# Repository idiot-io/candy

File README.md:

more at [idiot.io](idiot.io)

# candy
Electrodible lolliPCBpops

34c3 [video](https://www.youtube.com/watch?v=yhNaNCrcmBk) cooking show and talk  

## tools
using [inkscape](https://inkscape.org) with [svg2shenzen](https://github.com/badgeek/svg2shenzhen) extension - a wrapper/fork to [Kicad's](https://kicad.github.io) own bitmap2component plugin.  
basicly - design a board in SVG vector format and export it as gerber files, ready for fabrication.  

included in the repo is a script to automate the gerber file generation.  
so after you run `extensins>svg2shenzhen>export`  
run  
```python2 ../kicad_gerber_gen.py IRiotCandy-svg2shnzn.kicad_pcb```

[gerbv](http://gerbv.geda-project.org) was then used to preview the gerber output and move the silkscreen to its right position. if you have it in your path, the previous python script should auto open the generate dgerber files fo you.

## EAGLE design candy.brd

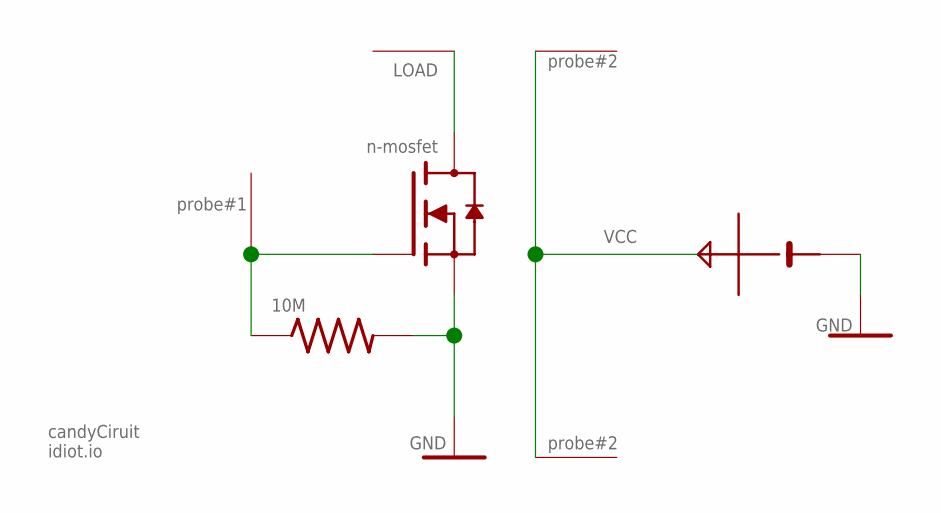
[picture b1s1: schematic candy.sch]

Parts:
10M: R-US_R1206; R1206
N-MOSFET: n-mosfet; SOT323
U$1, U$4, U$5: SMDPAD; PADSMD
U$7: CR2032LINX; CR2032-LINX
VCC: SMDPAD; PADSMD

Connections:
GND: 10M.2, N-MOSFET.2S (S), U$7.-
LOAD: N-MOSFET.3D (D), U$4.P$1
unnamed: 10M.1, N-MOSFET.1G (G), U$1.P$1
VCC: U$5.P$1, U$7.+, U$7.+2 (+), VCC.P$1

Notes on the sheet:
probe#1
probe#2
candyCiruit idiot.io

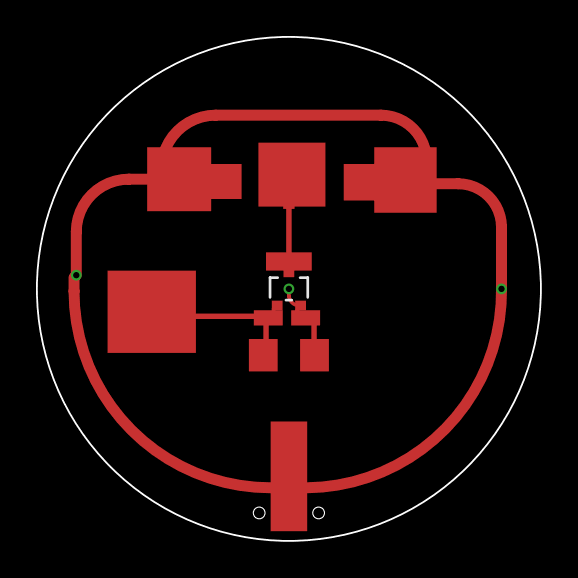
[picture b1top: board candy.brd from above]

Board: 2 copper layers, 28.0 x 28.0 mm, 7 parts (1 on the bottom side), 4 nets.

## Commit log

2018-03-08 inkscape svg
2018-03-08 layred for pdf2gerber
2018-03-08 eagle
2018-03-08 has candy, too big pads
2018-03-09 with ugly polygons on layout
2018-03-09 svg of eagle work
2018-03-09 added front
2018-03-10 BasicCandySilk update!
2018-03-10 BasicCandySilkScreenFinal
2018-03-10 BasicCandySilkFinal2
2018-03-10 FINALXXX
2018-03-12 fixed schema and added 2n222
2018-03-12 board ready for silk
2018-03-12 removed frame
2018-03-12 stright gerber
2018-03-12 folder
2018-03-13 shifted a bit
2018-03-15 CoinCellHolder
2018-03-15 coinCellDataSheet
2018-03-15 coinCell2models
2018-03-15 finall
2018-03-15 coinHolderPDF
2018-03-15 FINALLLL
2018-03-15 PDFFffffff
2018-05-16 no pours, smd and npn
2018-05-17 stick on front
2018-05-17 added svg, removed bmps
2018-05-17 gerber with svg2shanzen
2018-05-17 gerber ready
2018-05-18 3x3 and v1.0
2018-05-19 thermo cnady
2018-05-19 added mask
2018-05-19 bat back
2018-05-19 mask tweaks
2018-05-20 ModifiedSilkScreen
2018-05-20 updatedSilkSigns
2018-05-20 addedLM35Part
2018-05-21 resort
2018-05-21 removed dups
2018-05-22 IRiot candy
2018-05-22 reorder
2018-05-22 removed
2018-06-02 added Mosfet connections
2018-06-02 added v1.0 on back silk
2018-06-10 round vcc copper
2018-06-10 minor changs to iRiot board
2018-06-14 merged all files from IRiot repo
2018-06-15 shrink mask, and ass some silk guides
2018-06-15 silk/mask tweeks
2018-06-19 panelize in inkscape
2018-06-19 drills needs to be merged
2018-06-19 first gerber, need to remove copper aroudn drills
2018-06-19 some pics
2018-06-21 inkscape panel
2018-06-21 moved files
2018-06-22 panel 3mm border
2018-06-22 consolidated layers
2018-06-22 ready for multi panel
2018-06-22 3mm border gerbers
2018-06-23 new Graphics on krack
    added idiot.io logos on krakkk
2018-06-23 iirot esp8266 namechange
2018-06-23 added logos on Copper layer
    +changes
2018-06-23 final
2018-06-23 added IR&LED silk on IRiot
2018-06-23 added LM35
2018-06-23 added new GND GFX
    DONE!!!
2018-06-23 last!
2018-06-23 gitignore
2018-06-23 panel
2018-06-23 new panel
2018-06-24 wip mask
2018-06-25 draft panel, golden mask
2018-06-25 shrink edge top copper
2018-06-25 single
2018-06-26 upped the drill size to 0.4mm
2018-06-26 sent to fab
2018-06-27 thinner outlines, more back ground space
2018-07-03 nicer svg png
2018-07-05 restructure dirs
2018-07-09 add oled screen
2018-07-09 firemware comment
2018-07-10 post v1.1 changes #1
2018-07-10 added v1.2+
    all numbers are in seperate layer and
    also fixed logo silkscreen on both sides
2018-07-12 stick
2018-07-19 svg corrrections
2018-07-19 128x32 anel
2018-07-23 kicad idiot.io parts
2018-07-23 remove kicad lib to its own repo https://github.com/idiot-io/idiot-io-assets
2018-07-24 top breakouts
2018-07-25 bottom tab only
2018-07-26 bottom only tab
2018-08-01 flip led pin in iriot code, no random nec ir, svg bottom panel
2018-09-03 single basic
2018-12-23 G island
2018-12-23 v1.3
    fixed +3v and v1.3
2018-12-23 v1.3 throat
2018-12-24 releases folder
2018-12-24 release endyear
2019-01-30 added bitcraze svg2shnz
2019-01-30 renamed
2019-01-30 bitbadge svg2chnzn
2019-02-02 v1.0
2019-02-02 centered
2019-02-02 added name to b.silk
2019-02-02 Gpad fixed
2019-02-02 GpadMask fixed
2019-02-02 lastFixxxx
2019-02-03 mask
2019-02-03 mask and drills dist
2019-02-03 kicad export
2019-02-03 bitbadge sv2shnzn export
2019-02-03 newFix V1.0
2019-02-03 fixfixfixxx
2019-02-04 NewGpadFixation
2019-02-04 GND bridge at wrong layer fixfixfix
2019-02-04 fffix
2019-02-04 enlargeGpad+hole fixx
2019-02-05 moved up gnd>D trace
2019-02-06 bitCandy , plotted
2019-02-21 broke apart evil group in drill layer
2019-03-04 added sleep and lickometer circuit code
2019-03-05 comment
2019-03-06 IRiotV1.3 new design
2019-03-06 last finish
2019-03-06 IRriot gerber
2019-03-06 BitCandy1.1 New Version
2019-03-09 iriot and bitcandy to fab
2019-03-26 IRiotV1.4
    stick moved to front
    silk fix + Attiny85 Pads enlargment
2019-03-29 merged bitcandy version, 1.0>1.1
2019-03-29 merged IRriot versions 1.3>1.4
2019-04-22 fix for groups in drill
2019-04-30 BasicCandyV2.0 Next Generation!
2019-05-01 added a win bacth script to the export to plot stage
2019-05-01 script fix
2019-05-01 irriot 1.4 release
2019-08-03 Basic Candy NewGeneration V2.1
2019-08-03 Update BasicCandyV2.1.svg
    added Cu ring on back side
2019-08-03 Added Driil to Back Gate ring
2019-08-03 added castallation layer
2019-08-03 IRiotCandyV2.0 NewGeneration!
2019-08-03 sent to fab, corrected side plating, sideplating
2019-08-03 iriot v2
2019-08-04 tinyPadsFix
2019-08-05 BitCandyV2.0 NewGeneration!!!
2019-08-05 flipped BackSilk
2019-08-06 release for IRriotv2.0 fixed
2019-08-06 plot for BitCandy V2.0
2019-08-06 added png of both sides
2019-08-08 BackSilk Fixed
2019-08-18 VtoG short on back fixed!!
2019-08-18 front GateHole connected again!
2019-08-19 FIXXXed
2019-08-19 ungrouped
2019-08-25 new versionssss
2019-12-27 order
2019-12-27 NEU!
2019-12-27 gitignore and new asset
2019-12-27 resized
2019-12-27 another asset
2020-07-25 nicer blink up
2021-06-19 BitCandyStencil(Anyma2021)
2023-07-23 kicad 6 and py 3
2023-07-23 add gerbv preview
2023-07-23 1.2mm
2023-07-25 1.6mm
2023-07-25 sort names before gerbv
2023-07-26 add win grebv
2023-07-26 corrected stem
2023-07-26 split edge path into two paths
